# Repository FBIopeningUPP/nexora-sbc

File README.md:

# Nexora SBC

STM32MP157-based Single Board Computer

Trying to make this as nice as possible. Schematic done, working on PCB layout now.

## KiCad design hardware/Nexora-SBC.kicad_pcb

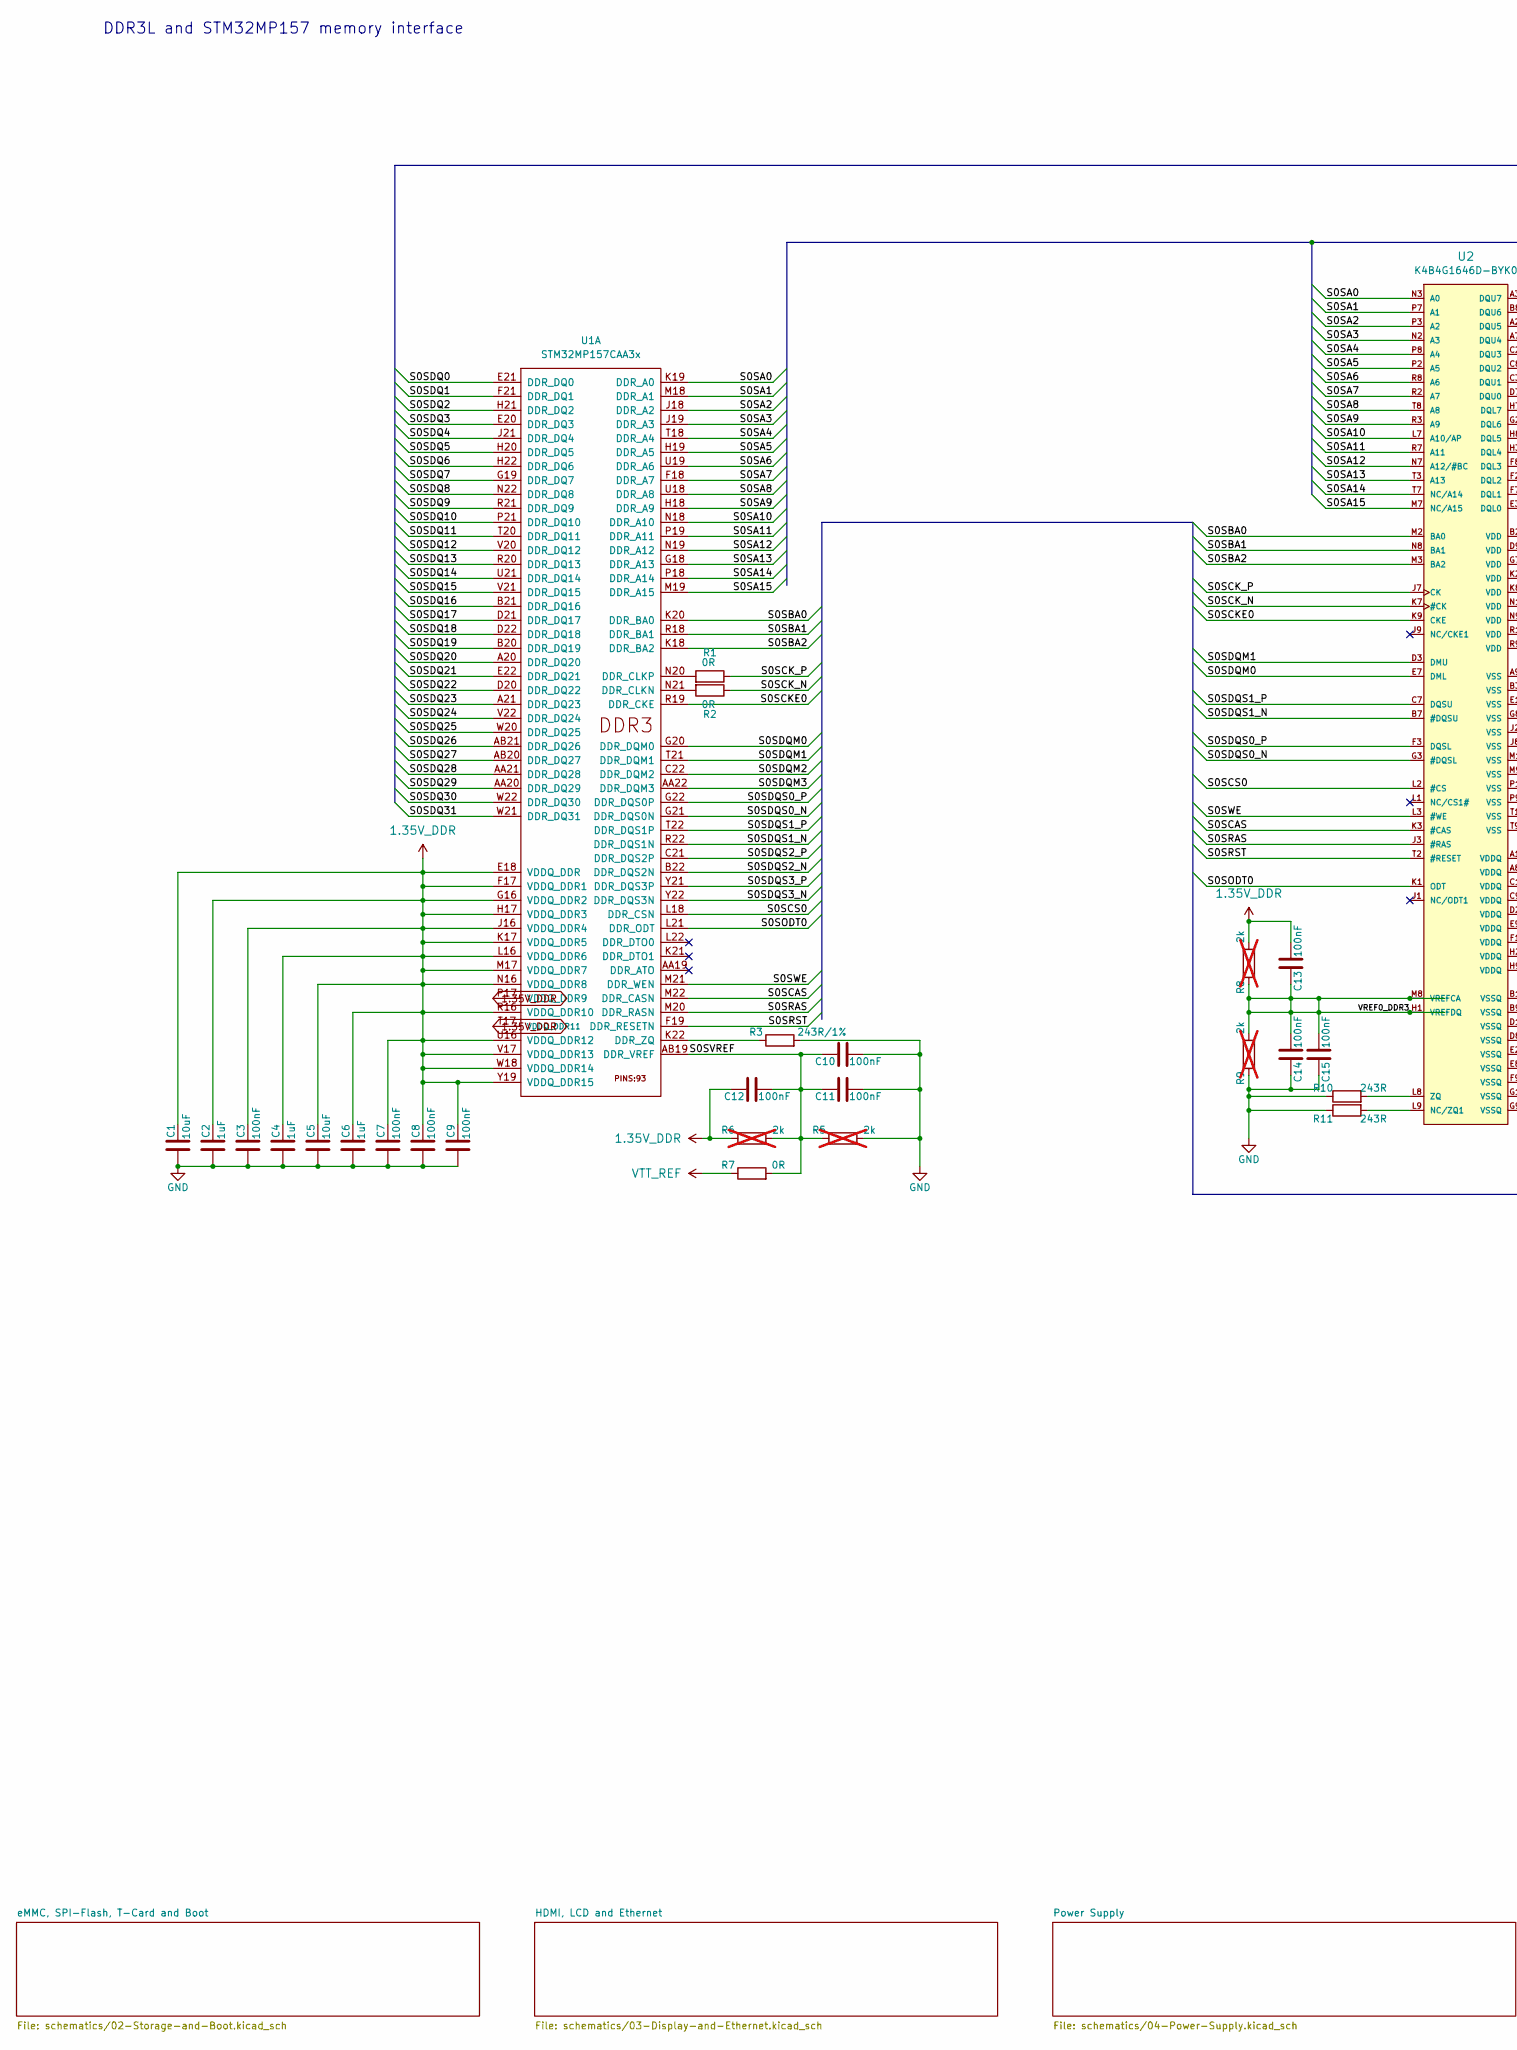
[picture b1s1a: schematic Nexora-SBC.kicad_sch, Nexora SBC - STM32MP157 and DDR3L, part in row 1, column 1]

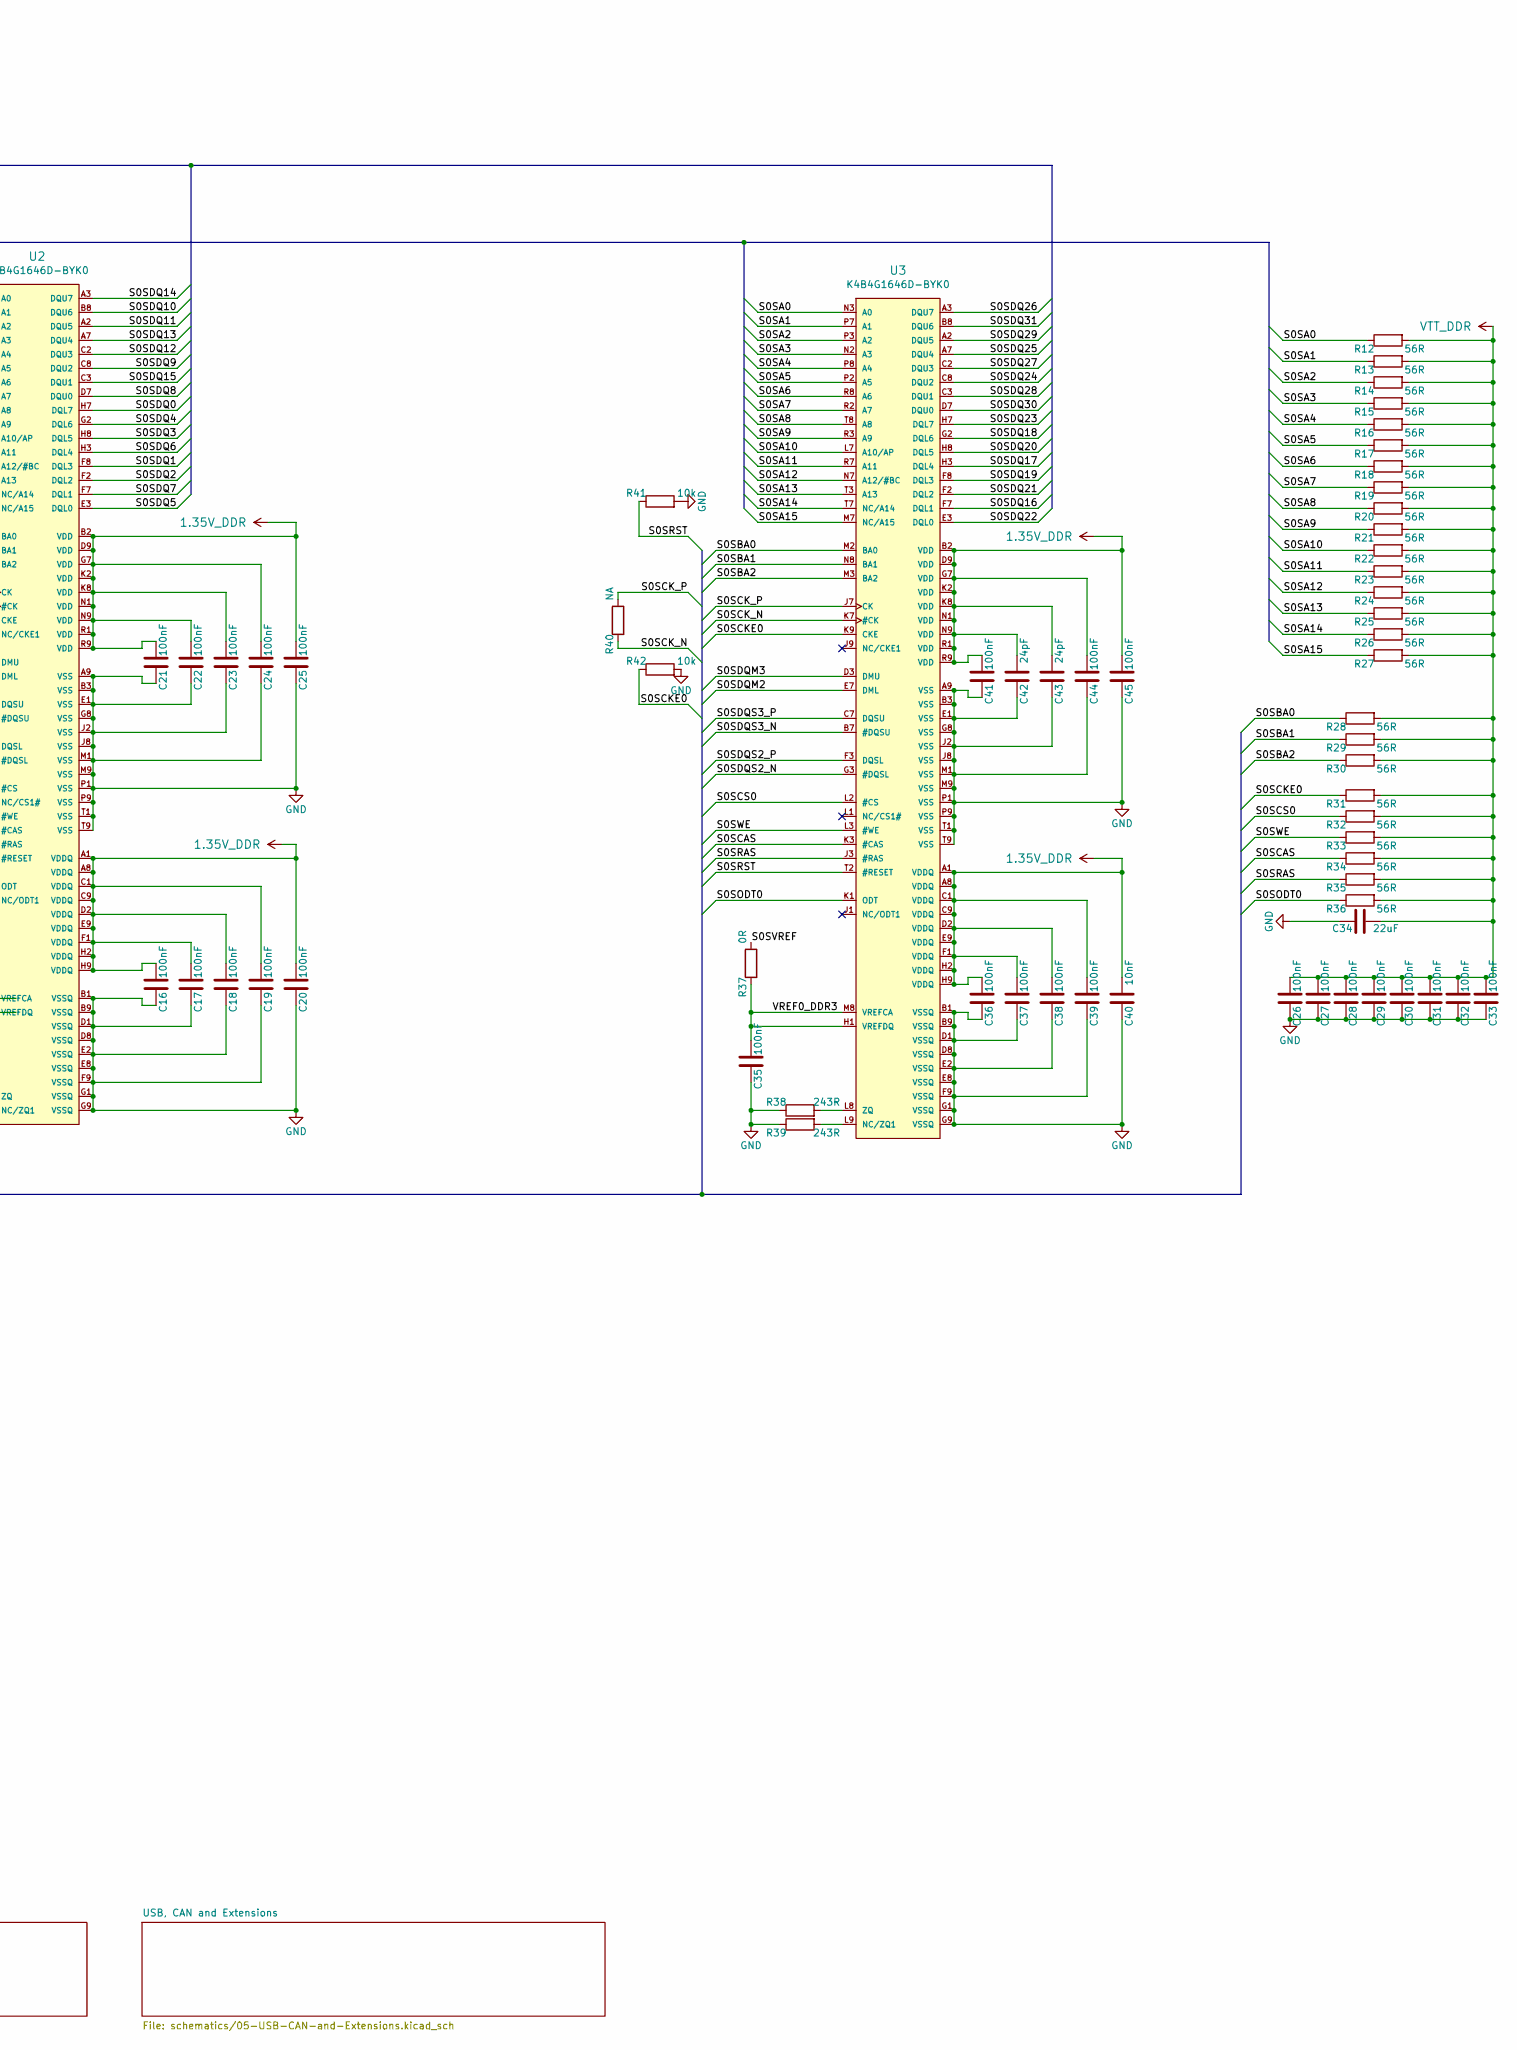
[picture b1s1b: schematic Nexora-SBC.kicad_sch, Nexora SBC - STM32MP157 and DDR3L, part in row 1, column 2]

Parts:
C1, C5: 10uF; C_0402_1005Metric
C2, C4, C6: 1uF; C_0402_1005Metric
C3, C7, C8, C9, C10, C11, C12, C13, C14, C15, C16, C17, C18, C19, C20, C21, C22, C23, C24, C25, C26, C27, C28, C29, C30, C31, C32, C33, C35, C36, C37, C38, C39, C41, C44, C45: 100nF; C_0402_1005Metric
C34: 22uF; C_0402_1005Metric
C40: 10nF; C_0402_1005Metric
C42, C43: 24pF; C_0402_1005Metric
R1, R2, R7, R37: 0R; R_0402_1005Metric
R3: 243R/1%; R_0402_1005Metric
R5, R6, R8, R9: 2k; R_0402_1005Metric; not fitted
R10, R11, R38, R39: 243R; R_0402_1005Metric
R12, R13, R14, R15, R16, R17, R18, R19, R20, R21, R22, R23, R24, R25, R26, R27, R28, R29, R30, R31, R32, R33, R34, R35, R36: 56R; R_0402_1005Metric
R40: NA; R_0402_1005Metric
R41, R42: 10k; R_0402_1005Metric
U1: STM32MP157CAA3x; LFBGA-448(Pitch-0.8mm_Pad-0.4mm_18x18x1.27mm)
U2, U3: K4B4G1646D-BYK0; FBGA96(HYNIX_SAMSUNG_512MX16_DDR3)

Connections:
1.35V_DDR: C1.1, C2.1, C3.1, C4.1, C5.1, C6.1, C7.1, C8.1, C9.1, C12.1, C13.2, C16.2, C17.2, C18.2, C19.2, C20.2, C21.2, C22.2, C23.2, C24.2, C25.2, C36.2, C37.2, C38.2, C39.2, C40.2, C41.2, C42.2, C43.2, C44.2, C45.2, R6.2, R8.1, U1.E18 (VDDQ_DDR), U1.F17 (VDDQ_DDR1), U1.G16 (VDDQ_DDR2), U1.H17 (VDDQ_DDR3), U1.J16 (VDDQ_DDR4), U1.K17 (VDDQ_DDR5), U1.L16 (VDDQ_DDR6), U1.M17 (VDDQ_DDR7), U1.N16 (VDDQ_DDR8), U1.P17 (VDDQ_DDR9), U1.R16 (VDDQ_DDR10), U1.T17 (VDDQ_DDR11), U1.U16 (VDDQ_DDR12), U1.V17 (VDDQ_DDR13), U1.W18 (VDDQ_DDR14), U1.Y19 (VDDQ_DDR15), U2.A1 (VDDQ), U2.A8 (VDDQ), U2.B2 (VDD), U2.C1 (VDDQ), U2.C9 (VDDQ), U2.D2 (VDDQ), U2.D9 (VDD), U2.E9 (VDDQ), U2.F1 (VDDQ), U2.G7 (VDD), U2.H2 (VDDQ), U2.H9 (VDDQ), U2.K2 (VDD), U2.K8 (VDD), U2.N1 (VDD), U2.N9 (VDD), U2.R1 (VDD), U2.R9 (VDD), U3.A1 (VDDQ), U3.A8 (VDDQ), U3.B2 (VDD), U3.C1 (VDDQ), U3.C9 (VDDQ), U3.D2 (VDDQ), U3.D9 (VDD), U3.E9 (VDDQ), U3.F1 (VDDQ), U3.G7 (VDD), U3.H2 (VDDQ), U3.H9 (VDDQ), U3.K2 (VDD), U3.K8 (VDD), U3.N1 (VDD), U3.N9 (VDD), U3.R1 (VDD), U3.R9 (VDD); also elsewhere on the board
/S0SA0: R12.2, U1.K19 (DDR_A0), U2.N3 (A0), U3.N3 (A0)
/S0SA1: R13.2, U1.M18 (DDR_A1), U2.P7 (A1), U3.P7 (A1)
/S0SA2: R14.2, U1.J18 (DDR_A2), U2.P3 (A2), U3.P3 (A2)
/S0SA3: R15.2, U1.J19 (DDR_A3), U2.N2 (A3), U3.N2 (A3)
/S0SA4: R16.2, U1.T18 (DDR_A4), U2.P8 (A4), U3.P8 (A4)
/S0SA5: R17.2, U1.H19 (DDR_A5), U2.P2 (A5), U3.P2 (A5)
/S0SA6: R18.2, U1.U19 (DDR_A6), U2.R8 (A6), U3.R8 (A6)
/S0SA7: R19.2, U1.F18 (DDR_A7), U2.R2 (A7), U3.R2 (A7)
/S0SA8: R20.2, U1.U18 (DDR_A8), U2.T8 (A8), U3.T8 (A8)
/S0SA9: R21.2, U1.H18 (DDR_A9), U2.R3 (A9), U3.R3 (A9)
/S0SA10: R22.2, U1.N18 (DDR_A10), U2.L7 (A10/AP), U3.L7 (A10/AP)
/S0SA11: R23.2, U1.P19 (DDR_A11), U2.R7 (A11), U3.R7 (A11)
/S0SA12: R24.2, U1.N19 (DDR_A12), U2.N7 (A12/#BC), U3.N7 (A12/#BC)
/S0SA13: R25.2, U1.G18 (DDR_A13), U2.T3 (A13), U3.T3 (A13)
/S0SA14: R26.2, U1.P18 (DDR_A14), U2.T7 (NC/A14), U3.T7 (NC/A14)
/S0SA15: R27.2, U1.M19 (DDR_A15), U2.M7 (NC/A15), U3.M7 (NC/A15)
/S0SBA0: R28.2, U1.K20 (DDR_BA0), U2.M2 (BA0), U3.M2 (BA0)
/S0SBA1: R29.2, U1.R18 (DDR_BA1), U2.N8 (BA1), U3.N8 (BA1)
/S0SBA2: R30.2, U1.K18 (DDR_BA2), U2.M3 (BA2), U3.M3 (BA2)
/S0SCAS: R34.2, U1.M22 (DDR_CASN), U2.K3 (#CAS), U3.K3 (#CAS)
/S0SCKE0: R31.2, R42.2, U1.R19 (DDR_CKE), U2.K9 (CKE), U3.K9 (CKE)
/S0SCK_N: R2.2, R40.2, U2.K7 (#CK), U3.K7 (#CK)
/S0SCK_P: R1.2, R40.1, U2.J7 (CK), U3.J7 (CK)
/S0SCS0: R32.2, U1.L18 (DDR_CSN), U2.L2 (#CS), U3.L2 (#CS)
/S0SDQ0: U1.E21 (DDR_DQ0), U2.H7 (DQL7)
/S0SDQ1: U1.F21 (DDR_DQ1), U2.F8 (DQL3)
/S0SDQ2: U1.H21 (DDR_DQ2), U2.F2 (DQL2)
/S0SDQ3: U1.E20 (DDR_DQ3), U2.H8 (DQL5)
/S0SDQ4: U1.J21 (DDR_DQ4), U2.G2 (DQL6)
/S0SDQ5: U1.H20 (DDR_DQ5), U2.E3 (DQL0)
/S0SDQ6: U1.H22 (DDR_DQ6), U2.H3 (DQL4)
/S0SDQ7: U1.G19 (DDR_DQ7), U2.F7 (DQL1)
/S0SDQ8: U1.N22 (DDR_DQ8), U2.D7 (DQU0)
/S0SDQ9: U1.R21 (DDR_DQ9), U2.C8 (DQU2)
/S0SDQ10: U1.P21 (DDR_DQ10), U2.B8 (DQU6)
/S0SDQ11: U1.T20 (DDR_DQ11), U2.A2 (DQU5)
/S0SDQ12: U1.V20 (DDR_DQ12), U2.C2 (DQU3)
/S0SDQ13: U1.R20 (DDR_DQ13), U2.A7 (DQU4)
/S0SDQ14: U1.U21 (DDR_DQ14), U2.A3 (DQU7)
/S0SDQ15: U1.V21 (DDR_DQ15), U2.C3 (DQU1)
/S0SDQ16: U1.B21 (DDR_DQ16), U3.F7 (DQL1)
/S0SDQ17: U1.D21 (DDR_DQ17), U3.H3 (DQL4)
/S0SDQ18: U1.D22 (DDR_DQ18), U3.G2 (DQL6)
/S0SDQ19: U1.B20 (DDR_DQ19), U3.F8 (DQL3)
/S0SDQ20: U1.A20 (DDR_DQ20), U3.H8 (DQL5)
/S0SDQ21: U1.E22 (DDR_DQ21), U3.F2 (DQL2)
/S0SDQ22: U1.D20 (DDR_DQ22), U3.E3 (DQL0)
/S0SDQ23: U1.A21 (DDR_DQ23), U3.H7 (DQL7)
/S0SDQ24: U1.V22 (DDR_DQ24), U3.C8 (DQU2)
/S0SDQ25: U1.W20 (DDR_DQ25), U3.A7 (DQU4)
/S0SDQ26: U1.AB21 (DDR_DQ26), U3.A3 (DQU7)
/S0SDQ27: U1.AB20 (DDR_DQ27), U3.C2 (DQU3)
/S0SDQ28: U1.AA21 (DDR_DQ28), U3.C3 (DQU1)
/S0SDQ29: U1.AA20 (DDR_DQ29), U3.A2 (DQU5)
/S0SDQ30: U1.W22 (DDR_DQ30), U3.D7 (DQU0)
/S0SDQ31: U1.W21 (DDR_DQ31), U3.B8 (DQU6)
/S0SDQM0: U1.G20 (DDR_DQM0), U2.E7 (DML)
/S0SDQM1: U1.T21 (DDR_DQM1), U2.D3 (DMU)
/S0SDQM2: U1.C22 (DDR_DQM2), U3.E7 (DML)
/S0SDQM3: U1.AA22 (DDR_DQM3), U3.D3 (DMU)
/S0SDQS0_N: U1.G21 (DDR_DQS0N), U2.G3 (#DQSL)
/S0SDQS0_P: U1.G22 (DDR_DQS0P), U2.F3 (DQSL)
/S0SDQS1_N: U1.R22 (DDR_DQS1N), U2.B7 (#DQSU)
/S0SDQS1_P: U1.T22 (DDR_DQS1P), U2.C7 (DQSU)
/S0SDQS2_N: U1.B22 (DDR_DQS2N), U3.G3 (#DQSL)
/S0SDQS2_P: U1.C21 (DDR_DQS2P), U3.F3 (DQSL)
/S0SDQS3_N: U1.Y22 (DDR_DQS3N), U3.B7 (#DQSU)
/S0SDQS3_P: U1.Y21 (DDR_DQS3P), U3.C7 (DQSU)
/S0SODT0: R36.2, U1.L21 (DDR_ODT), U2.K1 (ODT), U3.K1 (ODT)
/S0SRAS: R35.2, U1.M20 (DDR_RASN), U2.J3 (#RAS), U3.J3 (#RAS)
/S0SRST: R41.2, U1.F19 (DDR_RESETN), U2.T2 (#RESET), U3.T2 (#RESET)
/S0SVREF: C10.1, C11.1, C12.2, R5.2, R6.1, R7.1, R37.1, U1.AB19 (DDR_VREF)
/S0SWE: R33.2, U1.M21 (DDR_WEN), U2.L3 (#WE), U3.L3 (#WE)
/VREF0_DDR3: C13.1, C14.2, C15.2, C35.2, R8.2, R9.1, R37.2, U2.H1 (VREFDQ), U2.M8 (VREFCA), U3.H1 (VREFDQ), U3.M8 (VREFCA)
GND: C1.2, C2.2, C3.2, C4.2, C5.2, C6.2, C7.2, C8.2, C9.2, C10.2, C11.2, C14.1, C15.1, C16.1, C17.1, C18.1, C19.1, C20.1, C21.1, C22.1, C23.1, C24.1, C25.1, C26.1, C27.1, C28.1, C29.1, C30.1, C31.1, C32.1, C33.1, C34.1, C35.1, C36.1, C37.1, C38.1, C39.1, C40.1, C41.1, C42.1, C43.1, C44.1, C45.1, R3.1, R5.1, R9.2, R10.2, R11.2, R38.2, R39.2, R41.1, R42.1, U2.A9 (VSS), U2.B1 (VSSQ), U2.B3 (VSS), U2.B9 (VSSQ), U2.D1 (VSSQ), U2.D8 (VSSQ), U2.E1 (VSS), U2.E2 (VSSQ), U2.E8 (VSSQ), U2.F9 (VSSQ), U2.G1 (VSSQ), U2.G8 (VSS), U2.G9 (VSSQ), U2.J2 (VSS), U2.J8 (VSS), U2.M1 (VSS), U2.M9 (VSS), U2.P1 (VSS), U2.P9 (VSS), U2.T1 (VSS), U2.T9 (VSS), U3.A9 (VSS), U3.B1 (VSSQ), U3.B3 (VSS), U3.B9 (VSSQ), U3.D1 (VSSQ), U3.D8 (VSSQ), U3.E1 (VSS), U3.E2 (VSSQ), U3.E8 (VSSQ), U3.F9 (VSSQ), U3.G1 (VSSQ), U3.G8 (VSS), U3.G9 (VSSQ), U3.J2 (VSS), U3.J8 (VSS), U3.M1 (VSS), U3.M9 (VSS), U3.P1 (VSS), U3.P9 (VSS), U3.T1 (VSS), U3.T9 (VSS); also elsewhere on the board
unnamed: R2.1, U1.N21 (DDR_CLKN)
unnamed: R1.1, U1.N20 (DDR_CLKP)
unnamed: R3.2, U1.K22 (DDR_ZQ)
unnamed: R11.1, U2.L9 (NC/ZQ1)
unnamed: R10.1, U2.L8 (ZQ)
unnamed: R39.1, U3.L9 (NC/ZQ1)
unnamed: R38.1, U3.L8 (ZQ)
VTT_DDR: C26.2, C27.2, C28.2, C29.2, C30.2, C31.2, C32.2, C33.2, C34.2, R12.1, R13.1, R14.1, R15.1, R16.1, R17.1, R18.1, R19.1, R20.1, R21.1, R22.1, R23.1, R24.1, R25.1, R26.1, R27.1, R28.1, R29.1, R30.1, R31.1, R32.1, R33.1, R34.1, R35.1, R36.1; also elsewhere on the board
VTT_REF: R7.2; also elsewhere on the board

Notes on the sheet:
DDR3L and STM32MP157 memory interface
